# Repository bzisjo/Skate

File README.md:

# Skate
Skate Form Tracker

#AtmelStudio Setup for USBTinyISP + AVRDUDE
Download AVRDUDE from [here](http://www.nongnu.org/avrdude/). In AtmelStudio, go to Tools -> External Tools, and setup a new Menu content with the following parameterse:  
__Title:__ USBTiny ATmega328p  
__Command:__ (dir of AVRDUDE binary)\avrdude.exe  
__Argumnets:__ -c usbtiny -p atmega328p -U flash:w:$(TargetDir)$(TargetName).hex:i -C avrdude.conf -v  
__Initial Directory:__ (dir of AVRDUDE binary)  
  
Check the "Use Output window" option, and click OK.

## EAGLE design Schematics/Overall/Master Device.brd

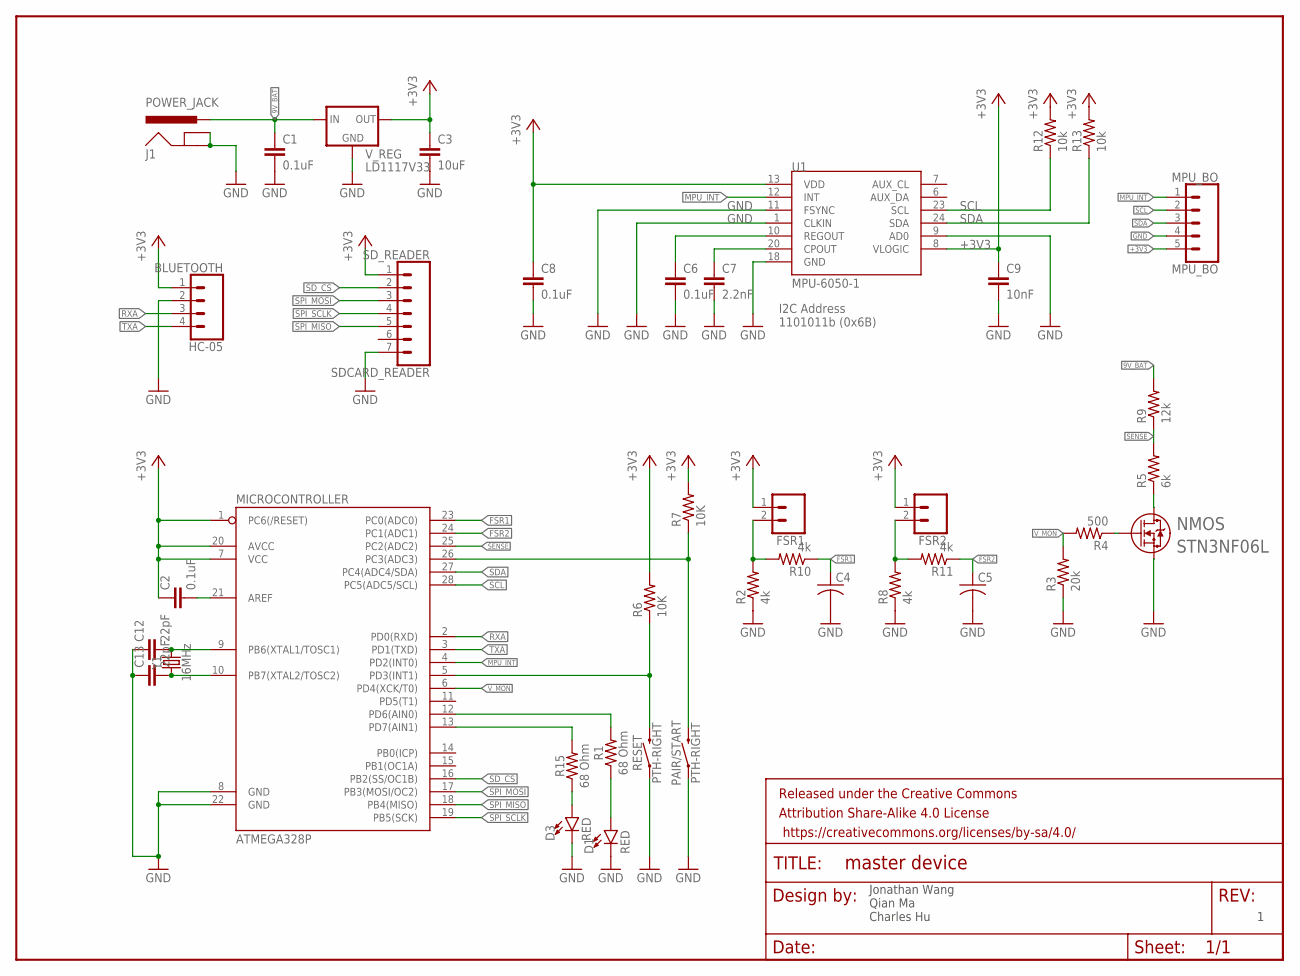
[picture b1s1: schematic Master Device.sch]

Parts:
C1, C2, C6, C8: 0.1uF; 0603-CAP
C3: 10uF; 0603-CAP
C4, C5: C-US050-050X075; C050-050X075
C7: 2.2nF; 0603-CAP
C9: 10nF; 0603-CAP
C12, C13: 22pF; 0603
D1, D3: RED; LED_3MM
FRAME1: FRAME-LETTERNO_PACKAGE; DUMMY
FSR1, FSR2: CONN_02; 1X02
HC-05: BLUETOOTH; 1X04
J1: POWER_JACK; POWER_JACK_PTH
MICROCONTROLLER: ATMEGA328P; DIP28
MPU_BO: MPU_BO; 1X05
NMOS: STN3NF06L; SOT-223
PAIR/START: PTH-RIGHT; TACTILE_SWITCH_PTH_RIGHT_ANGLE_KIT
R1, R15: 68 Ohm; 0603
R2, R8, R10, R11: 4k; 0603-RES
R3: 20k; 0603-RES
R4: 500; 0603-RES
R5: 6k; 0603-RES
R6, R7: 10K; 0603-RES
R9: 12k; 0603-RES
R12, R13: 10k; 0603-RES
RESET: PTH-RIGHT; TACTILE_SWITCH_PTH_RIGHT_ANGLE_KIT
SDCARD_READER: SD_READER; 1X07
U1: MPU-6050-1; QFN-24-4MM2
V_REG: LD1117V33; 78XXL
Y1: 16MHz; HC49US

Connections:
9V_BAT: C1.1, J1.PWR, R9.2, V_REG.OUT (IN)
+3V3: C2.1, C3.1, C8.1, C9.1, FSR1.1, FSR2.1, HC-05.1, MICROCONTROLLER.1 (PC6(/RESET)), MICROCONTROLLER.7 (VCC), MICROCONTROLLER.20 (AVCC), MPU_BO.5, R6.2, R7.2, R12.2, R13.2, SDCARD_READER.1, U1.8 (VLOGIC), U1.13 (VDD), V_REG.GND (OUT)
FSR1: C4.1, MICROCONTROLLER.23 (PC0(ADC0)), R10.1
FSR2: C5.1, MICROCONTROLLER.24 (PC1(ADC1)), R11.1
GND: C1.2, C3.2, C4.2, C5.2, C6.2, C7.2, C8.2, C9.2, C12.1, C13.1, D1.K (C), D3.K (C), HC-05.2, J1.GND, J1.GNDBREAK, MICROCONTROLLER.8 (GND), MICROCONTROLLER.22 (GND), MPU_BO.4, NMOS.3, PAIR/START.1, R2.1, R3.1, R8.1, RESET.1, SDCARD_READER.7, U1.1 (CLKIN), U1.9 (AD0), U1.11 (FSYNC), U1.18 (GND), V_REG.IN (GND)
MPU_INT: MICROCONTROLLER.4 (PD2(INT0)), MPU_BO.1, U1.12 (INT)
unnamed: C2.2, MICROCONTROLLER.21 (AREF)
unnamed: MICROCONTROLLER.5 (PD3(INT1)), R6.1, RESET.2
unnamed: MICROCONTROLLER.26 (PC3(ADC3)), PAIR/START.2, R7.1
unnamed: MICROCONTROLLER.12 (PD6(AIN0)), R1.2
unnamed: MICROCONTROLLER.13 (PD7(AIN1)), R15.2
unnamed: D3.A, R15.1
unnamed: D1.A, R1.1
unnamed: FSR1.2, R2.2, R10.2
unnamed: C7.1, U1.20 (CPOUT)
unnamed: C6.1, U1.10 (REGOUT)
unnamed: NMOS.1, R4.1
unnamed: NMOS.2, R5.1
unnamed: C13.2, MICROCONTROLLER.10 (PB7(XTAL2/TOSC2)), Y1.1
unnamed: FSR2.2, R8.2, R11.2
unnamed: C12.2, MICROCONTROLLER.9 (PB6(XTAL1/TOSC1)), Y1.2
RXA: HC-05.3, MICROCONTROLLER.2 (PD0(RXD))
SCL: MICROCONTROLLER.28 (PC5(ADC5/SCL)), MPU_BO.2, R12.1, U1.23 (SCL)
SDA: MICROCONTROLLER.27 (PC4(ADC4/SDA)), MPU_BO.3, R13.1, U1.24 (SDA)
SD_CS: MICROCONTROLLER.16 (PB2(SS/OC1B)), SDCARD_READER.2
SENSE: MICROCONTROLLER.25 (PC2(ADC2)), R5.2, R9.1
SPI_MISO: MICROCONTROLLER.18 (PB4(MISO)), SDCARD_READER.5
SPI_MOSI: MICROCONTROLLER.17 (PB3(MOSI/OC2)), SDCARD_READER.3
SPI_SCLK: MICROCONTROLLER.19 (PB5(SCK)), SDCARD_READER.4
TXA: HC-05.4, MICROCONTROLLER.3 (PD1(TXD))
V_MON: MICROCONTROLLER.6 (PD4(XCK/T0)), R3.2, R4.2

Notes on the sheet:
I2C Address 1101011b (0x6B)
Jonathan Wang Qian Ma Charles Hu

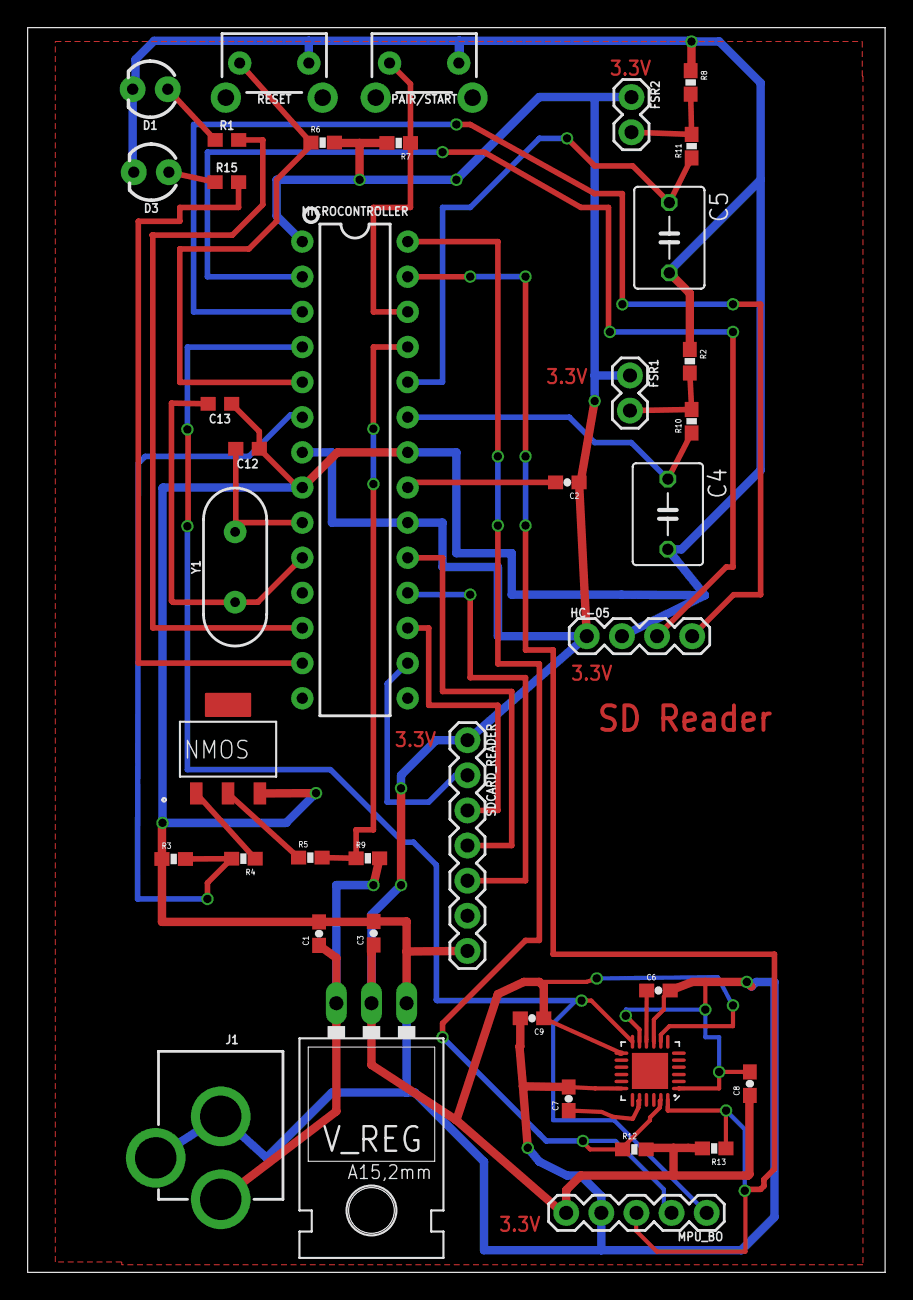
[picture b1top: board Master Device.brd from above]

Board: 2 copper layers, 62.0 x 90.0 mm, 41 parts (0 on the bottom side), 31 nets.

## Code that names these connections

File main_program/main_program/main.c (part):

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
	//Init interrupt
	PCICR |= (1 << PCIE1) | (1 << PCIE2);		//Set port-change interrupt to port C &D
	PCMSK1 |= (1 << PCINT11);	//Set port-change mask to PCINT11 (PC3)
	PCMSK2 |= (1 << PCINT19);   //set port-change mask to PCINT19 (PD3)
	//Init UART
	uart_init( UART_BAUD_SELECT_DOUBLE_SPEED(UART_BAUD_RATE,F_CPU) ); 

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					//approximately check battery volrage every 16s
					if(index % 500 == 0)
					{   //DIGITAL PIN TO TURN ON NMOS
						//enables PD4 as digital output and set PD4 HIGH

						DDRD |= (1 << PD4);
						PORTD |= (1 << PD4);
						fsr[2] = FSR_read(1);
						//let's do math here
						//fsr3 is a 8-bit value ranging from 0-255, correction factor k = (0.3943/0.3532)
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						state = 0;	
						error = 1; //*this is baaaaaaaaaaaaaad
						}
						PORTD &= ~(1 << PD4);
					}
					strcat(fatbuf, "\r\n");
					fat_write_file(fd, (uint8_t*) fatbuf, strlen(fatbuf));
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	//read pin25 value as voltage input
	if(i == 1)
	{
		ADMUX &= ~(1 << PORTC0);//clear PC0 bit
		ADMUX |= (1 << PORTC1); //enable pin25
	}
	else
	{
		ADMUX &= ~(1 << PORTC1);//clear PC1 bit, disable pin25
		ADMUX ^= (1 << PORTC0); //toggle between pin23 and 24	
	}
	// start ADC conversion
	ADCSRA |= (1 << ADSC);		
	// wait here until the chip clears the ADSC bit for us, which means the ADC is complete			
	while(bit_is_set(ADCSRA, ADSC)) {}	
	// toggle ADMUX PC0 bit to switch between pin23 and pin24				
				
	return ADCH;
}
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
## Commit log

2017-03-10 Updated Master with battery sensor
2017-03-13 Added working UART Library for AVR
    Also MPU6050 AVR Library, yet to be successfully implemented
2017-03-14 Finalized Schematics
2017-03-15 worked on pcb layout
2017-03-16 eagle cad is cancer
2017-03-16 Finished this fucking piece of shit
2017-03-16 Added shape node to bottom for GND
2017-03-16 plz check my bullshit
2017-03-16 Im done with this shit
2017-03-22 Read commet details
    External clock is used (LFuse 0xFF)
    System still at 3.3V (although 5V is suggested, things seem to function as of now)
    Getting raw data from the IMU works. Remember to set the SCL_CLOCK
2017-03-27 I'm not sure what changed. But here are changes.
2017-03-28 Figured out uSD stuff
    Sort of.
2017-03-29 Gerber final round
2017-03-31 test data for imu
2017-04-04 Implemented a complimentary filter
2017-04-04 arduino_test
2017-04-05 arduino code change
2017-04-07 microcontroller does not freeze anymore. added data of complimentary filter with different tau values
2017-04-09 added tau = 0.1 test
2017-04-09 changed name of capture_01.txt to capture_tau01.txt
2017-04-09 Added more tests for tau values of the compilmentary filter
2017-04-09 retested tau values from yesterday
2017-04-09 updated tau = 0.9
2017-04-09 Usart_tset
2017-04-09 Design Review
    Pls update the R&V by tomorrow
2017-04-09 Merge branch 'master' into chu
    added smaller tau valued tests
2017-04-09 implemented runge-kutta integrator
2017-04-09 test some of code and did some data collection for configuring the IMU
2017-04-10 Movement tests of raw convertion data
2017-04-10 requirement_changed
2017-04-10 rvchange
2017-04-10 added matlab script for analysing IMU capture data
2017-04-10 Merge branch 'master' into chu
    changed 2 numbers in IMU rv table to make easier to get points
2017-04-10 Translational testing with points every 10 ms
2017-04-10 Merge branch 'master' into chu
    did tests with 50ms reads because 10 ms reads were not getting captured correctly
2017-04-10 Tests for 100ms becaues 50ms did not give full data capture
2017-04-10 updated matlab script
2017-04-10 RV update
2017-04-10 This file contains all the RV tables
    Feel free to print it out and cross off items from the list
2017-04-10 MESSY UART
2017-04-10 more scripts
2017-04-14 IS IT? IS IT A BAD THING?
2017-04-18 slight code changes and had a dump
2017-04-18 took new dump
2017-04-18 added trace dump
2017-04-18 fixed 10ms data and updated script
2017-04-18 deleted trc file
2017-04-18 verification test with matlab timestamps
2017-04-18 used unix time stamp
2017-04-18 used ymdhs
2017-04-18 added more to script
2017-04-18 Started main program
2017-04-18 added rotational 10 ms tests of raw data
2017-04-19 Main program in progress
2017-04-19 undid library's own inaccurate calibratations and ran some tests
2017-04-19 finished testing all degrees
2017-04-19 removed first row of each test to make in line with matlab
2017-04-19 Prototype done
2017-04-19 verification of low pass filter
2017-04-19 fsr and timer
2017-04-20 Added some LED stuff. Doesn't compile.
2017-04-20 fixes
2017-04-20 added nmos Vbattery monitoring part1
2017-04-20 scripting add
2017-04-20 calibrated other imu and did mahony rotation tests
2017-04-20 fixed previous tests
2017-04-21 Vbattery part2
2017-04-21 Things work
2017-04-21 added kutta runge integrator
2017-04-21 added documentation of lpf verification
2017-04-24 added drop tests
2017-04-24 4g range drop test
2017-04-24 raw yaw test
2017-04-24 continued scripting and making sense of IMU
2017-04-25 comp filter, lpf, drop tests
2017-04-25 revised rv table
2017-04-25 made correction of 5 DOM instead of 6
2017-04-25 rv IMU
2017-04-25 some added file
2017-04-25 edited imu verification
2017-04-26 tests on arduino
2017-04-26 More things work ^_^
2017-04-26 added second still arduino test
2017-04-26 added files with all of my coded functions: mpu6050filtering.c and mpu6050filtering.h
2017-04-26 Silly mistakes have been fixed
2017-04-26 Reenabled all of the nmos circuits
2017-04-26 Moved the sd partition part
2017-04-26 Added counter and fixed shit
2017-04-26 Added data
2017-04-27 started on gui and looked at skate test data
2017-04-27 finished mvp of gui
2017-04-27 Added masterdata (2)
2017-04-27 scripted and worked on gui
2017-04-27 asv files were removed
2017-04-27 finished gui with dank memes
2017-05-02 fixed some plots for paper and pres
2017-05-02 some screen shots
2017-05-03 graphs
2017-05-04 pics

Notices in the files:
parts and their libraries:
SparkFun-LED: Licensing: Creative Commons ShareAlike 4.0 International - https://creativecommons.org/licenses/by-sa/4.0
SparkFun-Aesthetics: Released under the Creative Commons Attribution Share-Alike 4.0 License
SparkFun-Aesthetics: https://creativecommons.org/licenses/by-sa/4.0
